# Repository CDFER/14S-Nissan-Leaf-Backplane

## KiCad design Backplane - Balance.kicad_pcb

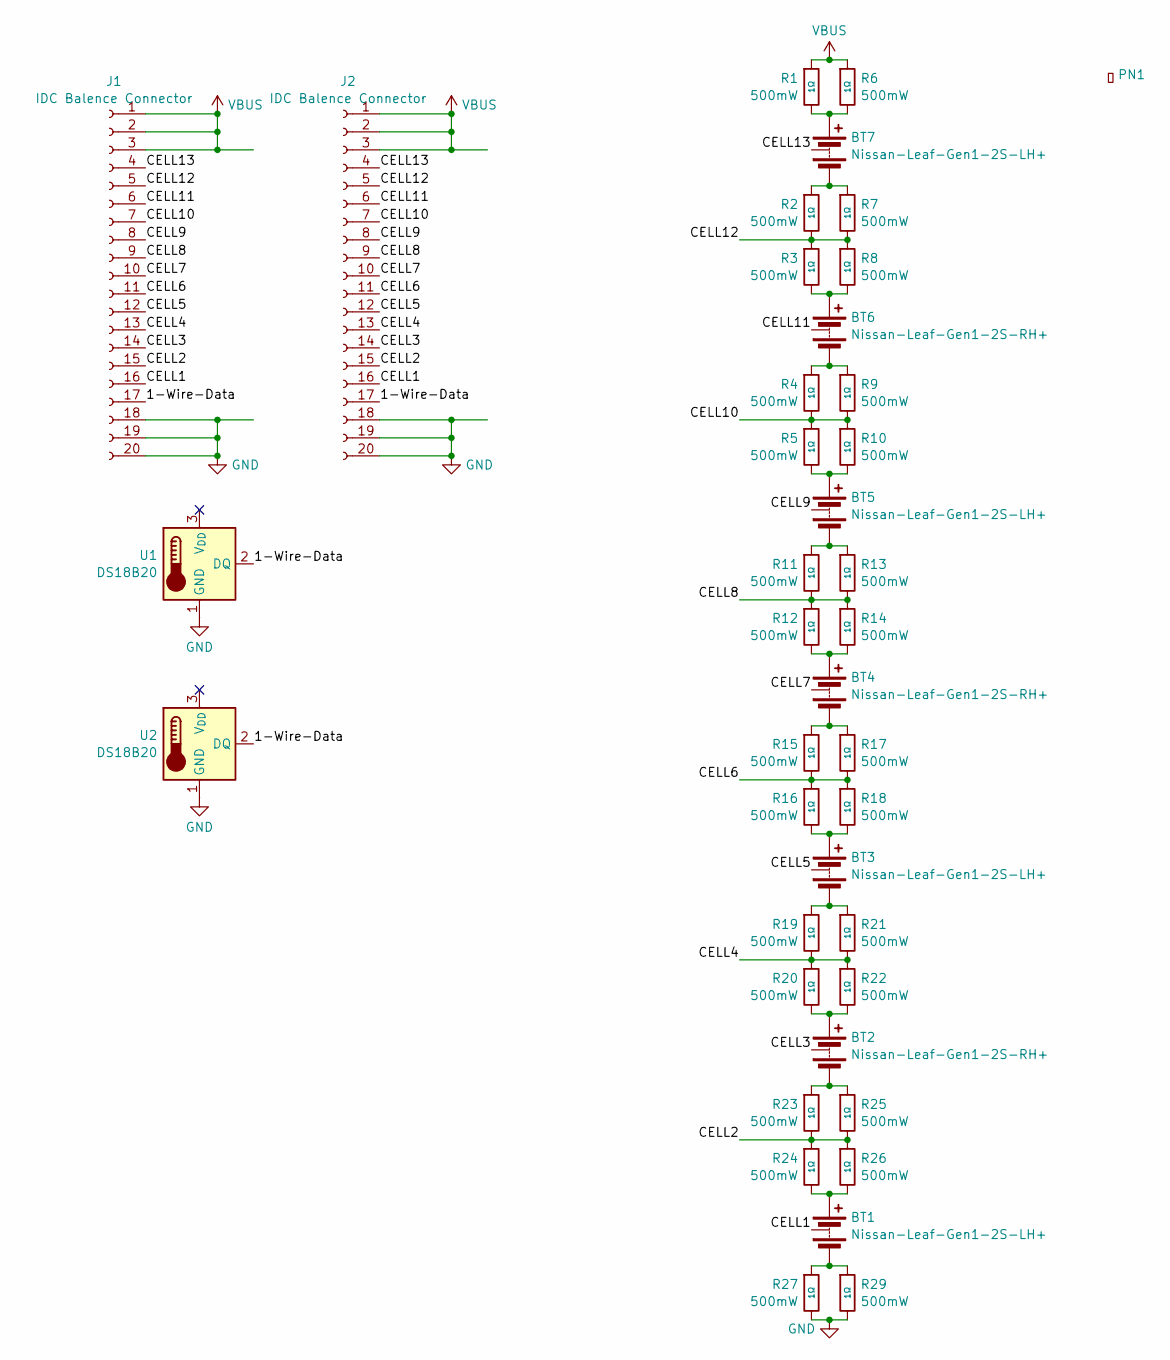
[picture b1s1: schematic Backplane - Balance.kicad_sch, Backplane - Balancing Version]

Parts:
BT1, BT3, BT5, BT7: Nissan-Leaf-Gen1-2S-LH+
BT2, BT4, BT6: Nissan-Leaf-Gen1-2S-RH+
J1, J2: IDC Balence Connector; IDC-Header_2x10_P2.54mm_Vertical
PN1: Part_Num_JLCPCB
R1, R2, R3, R4, R5, R6, R7, R8, R9, R10, R11, R12, R13, R14, R15, R16, R17, R18, R19, R20, R21, R22, R23, R24, R25, R26, R27, R29: 1Ω; R_1206
U1, U2: DS18B20; TO-92_Inline_Horizontal1

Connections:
/1-Wire-Data: J1.17, J2.17, U1.2 (DQ), U2.2 (DQ)
/CELL1: BT1.2 (-), J1.16, J2.16
/CELL2: J1.15, J2.15, R23.2, R24.1, R25.2, R26.1
/CELL3: BT2.2 (-), J1.14, J2.14
/CELL4: J1.13, J2.13, R19.2, R20.1, R21.2, R22.1
/CELL5: BT3.2 (-), J1.12, J2.12
/CELL6: J1.11, J2.11, R15.2, R16.1, R17.2, R18.1
/CELL7: BT4.2 (-), J1.10, J2.10
/CELL8: J1.9, J2.9, R11.2, R12.1, R13.2, R14.1
/CELL9: BT5.2 (-), J1.8, J2.8
/CELL10: J1.7, J2.7, R4.2, R5.1, R9.2, R10.1
/CELL11: BT6.2 (-), J1.6, J2.6
/CELL12: J1.5, J2.5, R2.2, R3.1, R7.2, R8.1
/CELL13: BT7.2 (-), J1.4, J2.4
GND: J1.18, J1.19, J1.20, J2.18, J2.19, J2.20, R27.2, R29.2, U1.1 (GND), U2.1 (GND)
unnamed: BT1.1 (+), R24.2, R26.2
unnamed: BT1.3 (-), R27.1, R29.1
unnamed: BT2.1 (+), R20.2, R22.2
unnamed: BT2.3 (-), R23.1, R25.1
unnamed: BT3.1 (+), R16.2, R18.2
unnamed: BT3.3 (-), R19.1, R21.1
unnamed: BT4.1 (+), R12.2, R14.2
unnamed: BT4.3 (-), R15.1, R17.1
unnamed: BT5.1 (+), R5.2, R10.2
unnamed: BT5.3 (-), R11.1, R13.1
unnamed: BT6.1 (+), R3.2, R8.2
unnamed: BT6.3 (-), R4.1, R9.1
unnamed: BT7.1 (+), R1.2, R6.2
unnamed: BT7.3 (-), R2.1, R7.1
VBUS: J1.1, J1.2, J1.3, J2.1, J2.2, J2.3, R1.1, R6.1

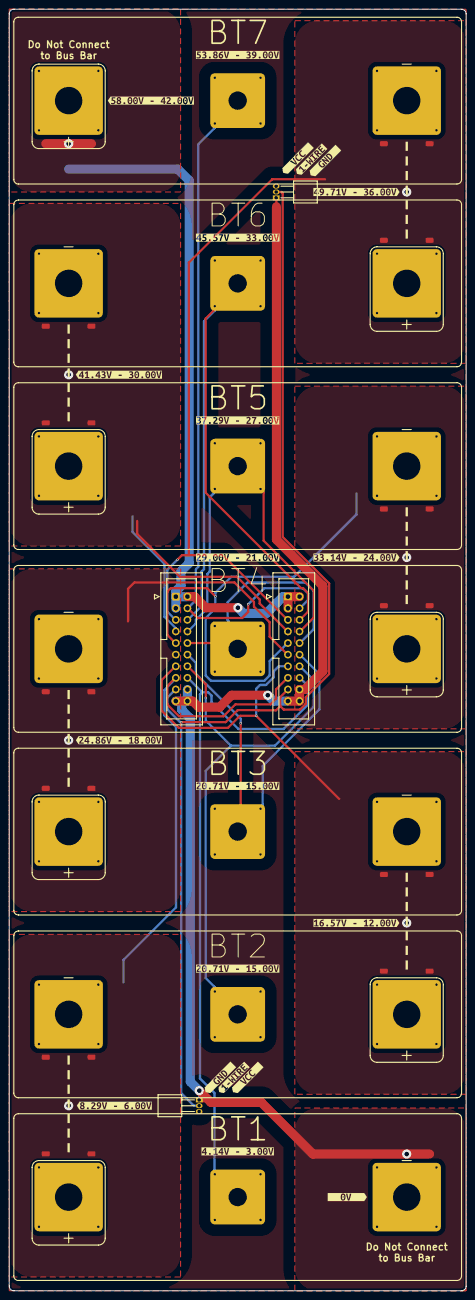
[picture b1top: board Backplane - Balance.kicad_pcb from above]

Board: 2 copper layers, 100.0 x 280.5 mm, 61 parts (1 on the bottom side), 30 nets.

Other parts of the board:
kibuzzard-680EEA00, kibuzzard-680EEA00#2: G***; kibuzzard-680EEA00
kibuzzard-680EEA19, kibuzzard-680EEA19#2: G***; kibuzzard-680EEA19
kibuzzard-680EEA42, kibuzzard-680EEA42#2: G***; kibuzzard-680EEA42
kibuzzard-680EEAED: G***; kibuzzard-680EEAED
kibuzzard-680EF0B4: G***; kibuzzard-680EF0B4
kibuzzard-680EF1BA: G***; kibuzzard-680EF1BA
kibuzzard-680EF1E5: G***; kibuzzard-680EF1E5
kibuzzard-680EF2D1: G***; kibuzzard-680EF2D1
kibuzzard-680EF2FD: G***; kibuzzard-680EF2FD
kibuzzard-680EF17D: G***; kibuzzard-680EF17D
kibuzzard-680EF18E: G***; kibuzzard-680EF18E
kibuzzard-680EF51A: G***; kibuzzard-680EF51A
kibuzzard-680EF59B: G***; kibuzzard-680EF59B
kibuzzard-680EF203: G***; kibuzzard-680EF203
kibuzzard-680EF230: G***; kibuzzard-680EF230
kibuzzard-680EF343: G***; kibuzzard-680EF343
kibuzzard-680EF361: G***; kibuzzard-680EF361
kibuzzard-680EF474: G***; kibuzzard-680EF474

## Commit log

2025-04-22 V1 Backplane PCB
2025-04-28 Reroute using TopoR
2025-04-28 - Added Balance Version - Added Images - Added Battery .step
2025-05-15 Last changes for V1
